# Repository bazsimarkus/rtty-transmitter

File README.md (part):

# rtty-transmitter

An ATmega328P-based AM/RTTY transmitter card with USB serial control, Direct Digital Synthesis audio generation, PCM audio playback from SPI EEPROM, and a Wien bridge oscillator RF stage. The board is controlled entirely through an AT command interface over a virtual COM port, and includes a companion Python control center application for Windows, Linux, and macOS.

---

## Table of Contents

- [Overview](#overview)
- [Features](#features)
- [Hardware Description](#hardware-description)
  - [USB Interface and Power Supply](#usb-interface-and-power-supply)
  - [Microcontroller](#microcontroller)
  - [DAC and DDS Engine](#dac-and-dds-engine)
  - [EEPROM for PCM Audio Storage](#eeprom-for-pcm-audio-storage)
  - [Virtual Ground](#virtual-ground)
  - [Wien Bridge Oscillator and Carrier Wave](#wien-bridge-oscillator-and-carrier-wave)
  - [Audio Buffer](#audio-buffer)
  - [RF Output Stage](#rf-output-stage)
  - [Tank Circuit and Antenna Output](#tank-circuit-and-antenna-output)
  - [Signal Chain Summary](#signal-chain-summary)
  - [GPIO Expansion and Status LED](#gpio-expansion-and-status-led)
  - [Bill of Materials](#bill-of-materials)
  - [PCB](#pcb)
- [Firmware](#firmware)
  - [AT Command Interface](#at-command-interface)
  - [RTTY Encoding](#rtty-encoding)
  - [PCM Audio Playback](#pcm-audio-playback)
  - [EEPROM Upload Protocol](#eeprom-upload-protocol)
- [Getting Started](#getting-started)
  - [Requirements](#requirements)
  - [Drivers](#drivers)
  - [Connecting the Board](#connecting-the-board)
- [Building and Flashing the Firmware](#building-and-flashing-the-firmware)
  - [Command-Line Build with avr-gcc and avrdude](#command-line-build-with-avr-gcc-and-avrdude)
  - [Building with MPLAB X IDE](#building-with-mplab-x-ide)
- [Control Center Application](#control-center-application)
  - [Installation](#installation)
  - [Usage](#usage)
- [Antenna Selection and Range](#antenna-selection-and-range)
- [Testing and Reception](#testing-and-reception)
- [Comparison with Official RTTY](#comparison-with-official-rtty)
- [Regulatory Notice](#regulatory-notice)
- [Personal Note](#personal-note)

---

## Overview

This project is a self-contained AM/RTTY transmitter card designed and built around the ATmega328P microcontroller. The board generates FSK (Frequency Shift Keying) audio tones using a software Direct Digital Synthesis engine, feeds those tones through an 8-bit SPI DAC, buffers and amplifies them through a dual op-amp stage, and then modulates them onto a carrier wave produced by a Wien bridge oscillator running at approximately 802 kHz. The resulting AM signal is delivered to an SMA connector for antenna connection.

The board is powered and controlled through a single USB Type B cable. An MCP2221A USB-to-UART bridge makes the board appear as a standard COM port on the host computer, requiring no custom drivers beyond the standard MCP2221 package. All board functions are controlled through a straightforward AT command interface at 9600 baud. A Python-based control center application is included in the tools folder to provide a graphical interface for all features, including RTTY message transmission, text file transmission, PCM audio upload and playback, and GPIO control.

The board can also function as an audio transmitter: an 8-bit, 8 kHz PCM audio file can be uploaded to the onboard 25LC1024 SPI EEPROM (128 KB) and played back over the air using the AT+play command, AM-modulating the 802 kHz carrier with audio content.

---

## Features

- RTTY transmission using ITA-2 Baudot encoding over AM
- Configurable mark/space frequencies and baud rate via AT commands (defaults: MARK 2125 Hz, SPACE 2295 Hz, 45.45 baud)
- Direct Digital Synthesis sine wave generation at 80 kHz sample rate via Timer1 interrupt
- MCP4901 8-bit SPI DAC output
- 25LC1024 SPI EEPROM (128 KB) for PCM audio sample storage
- 8 kHz PCM audio playback from EEPROM via Timer2 interrupt, AM-modulating the carrier
- Wien bridge oscillator carrier wave at approximately 802 kHz
- Current-modulated cascode RF output stage (PN2222A BJTs)
- Tank circuit output filter with loading coil and SMA antenna connector
- MCP2221A USB-to-UART bridge, appearing as a standard COM port at 9600 8N1
- Powered entirely from USB (5V, USB Type B connector)
- Five user-accessible GPIO pins on a 2x5 pin header (J3), including onboard status LED control
- AVR ISP 10-pin shrouded box header for firmware flashing with USBasp or compatible programmer
- 120 x 60 mm, two-layer FR-4 PCB, designed in KiCad 7 and finalized in KiCad 9
- Companion Python control center application for Windows, Linux, and macOS

---

## Hardware Description

### USB Interface and Power Supply

The board is connected to a host PC through a USB Type B connector (J1). Power is drawn from the USB 5V rail and distributed across the board through decoupling capacitors at each IC supply pin.

The USB-to-UART bridge is the MCP2221A (U1), a 14-pin DIP chip from Microchip. When connected, it presents itself to the operating system as a virtual COM port, allowing any standard serial terminal or the included control center application to communicate with the ATmega328P at 9600 8N1. No special kernel modules are required on most systems, though the MCP2221 driver package from Microchip's website may need to be installed on Windows for the COM port to appear. The driver can be downloaded from Microchip's product page for the MCP2221A.

### Microcontroller

The central processing element is the ATmega328P (U2), a 28-pin DIP AVR microcontroller running from a 16 MHz crystal (Y1) with no clock prescaler. It handles all firmware tasks: UART communication with the host through the MCP2221A, hardware SPI to the MCP4901 DAC, bit-bang SPI to the 25LC1024 EEPROM, GPIO control, and the two timer-driven interrupt service routines that form the core of the signal generation pipeline.

The reset line is connected through a capacitor to the DTR signal of the MCP2221A, allowing the control center application to reset the board on connect. A 10-pin shrouded box header (J2) exposes the AVR ISP signals (RESET, SCK, MISO, MOSI) for firmware flashing with a USBasp or compatible programmer.

### DAC and DDS Engine

The MCP4901 (U3) is an 8-bit, single-channel SPI DAC in an 8-pin DIP package. It receives samples from the ATmega328P over hardware SPI running at 8 MHz (F_CPU/2 with SPI2X). Timer1 is configured in CTC mode with OCR1A = 199 and no prescaler, producing an interrupt rate of exactly 80 kHz (16 MHz / 200). Each interrupt advances a 32-bit DDS phase accumulator by a pre-computed increment that determines the output frequency:

```
phase_increment = frequency x 2^32 / 80000
```

The upper 8 bits of the phase accumulator index into a 256-entry sine table stored in SRAM, and the resulting sample is written to the DAC in the same ISR. This produces a clean, digitally synthesized sine wave at the desired audio frequency with a sample rate of 80 kHz, giving well over 40 kHz of usable bandwidth and negligible harmonic content in the RTTY audio band. Setting the phase increment to zero mutes the carrier between transmissions.

For RTTY, the firmware uses two phase increments corresponding to the mark and space frequencies. Bit timing is achieved by loading a tick counter in the same ISR: for 45.45 baud, each bit lasts 80000 / 45.45 = 1760 Timer1 ticks, which equals exactly 22 ms.

### EEPROM for PCM Audio Storage

The 25LC1024 (U4) is a 1 Mbit (131072 byte) SPI EEPROM in an 8-pin DIP package. It is connected to the ATmega328P through a bit-bang SPI interface on PORTC (PC0 = /CS, PC3 = MOSI, PC4 = SCK, PC5 = MISO). A separate bit-bang interface is used for the EEPROM rather than the hardware SPI port so that the hardware SPI bus remains dedicated to the DAC and the time-critical 80 kHz Timer1 ISR is not disrupted by EEPROM accesses.

The EEPROM stores 8-bit unsigned PCM audio samples at 8 kHz. During playback, Timer1 is suspended and Timer2 takes over, configured in CTC mode to fire at exactly 8 kHz (OCR2A = 249, prescaler /8 on a 16 MHz clock). Each Timer2 ISR reads one byte from the EEPROM via bit-bang SPI and writes it directly to the DAC, producing an audio waveform that AM-modulates the carrier. End of audio is signaled by 250 consecutive 0xFF samples, which at 8 kHz corresponds to approximately 31 ms of silence, making it a reliable sentinel value.

### Virtual Ground

The MCP6022 op-amp and the rest of the analog circuit are powered from a single 5V USB supply, which means the supply voltage goes from 0V (GND) to 5V and nothing below. The problem is that a sine wave needs to swing both up and down around a center point. If the center point is 0V, the negative half of the wave would require a negative voltage, which we simply don't have.

The solution is to create a "virtual ground" at 2.5V, a stable mid-point that the op-amp can treat as its reference. The sine wave then swings from around 1.5V up to 3.5V, which looks like ±1V when measured relative to this 2.5V center. The next stage (the transistor base) receives the signal through a coupling capacitor, which strips away the 2.5V DC offset and leaves only the AC swing.

R15 (10k) and R16 (10k) form a simple voltage divider between the 5V supply and GND. Because both resistors are the same value, the midpoint sits at exactly 2.5V. C17 (10uF) is a bypass capacitor connected from this midpoint to GND. It acts like a reservoir that keeps the 2.5V stable and prevents it from wobbling when the op-amp draws current from it. Without this capacitor, the virtual ground voltage would fluctuate with the signal, causing distortion. The virtual ground node is labeled VIRTUAL GROUND in the schematic and is accessible at test point TP1 on the PCB.

### Wien Bridge Oscillator and Carrier Wave

The carrier wave is generated by the first op-amp inside the MCP6022 chip (U5A). It is wired as a Wien bridge oscillator, which is a circuit that produces a sine wave on its own with no input signal (it just runs continuously once power is applied).

The basic idea is that the op-amp has two feedback paths. The first path goes from the output back to the non-inverting input (the "+" pin) and is frequency-selective (it only passes signals at one specific frequency with the right timing to keep the oscillation going). The second path goes from the output back to the inverting input (the "−" pin) and sets the gain. If the gain is slightly above 1 at that specific frequency, the circuit amplifies its own tiny noise until it builds into a stable sine wave.

The frequency is set by R23 (1.5k) and R14 (1.5k) together with C18 (100pF) and C15 (100pF). These four components form the frequency-selective network on the non-inverting input. One resistor-capacitor pair (R14 and C15) connects from the non-inverting input to the virtual ground. The other pair (R23 and C18) connects from the non-inverting input back to the output. This arrangement only passes the right frequency and phase combination to keep the oscillator running. The resonant frequency works out to approximately 802 kHz, which sits in the AM medium-wave broadcast band, meaning any standard AM kitchen radio can receive the signal without special equipment.

```
f = 1 / (2 x pi x R x C)
  = 1 / (2 x pi x 1500 x 100e-12)
  = approximately 802 kHz
```

The gain is set by R22 (15k) and R19 (4.7k). R19 connects from the inverting input ("−" pin, pin 2) to the virtual ground, and R22 connects from the inverting input back to the output. The ratio of these two resistors sets the amplification to just above 3, which is the minimum needed to sustain oscillation in a Wien bridge.

The problem with setting the gain slightly above 3 is that without any correction, the wave would just keep growing until it hits the supply rails and becomes a clipped square wave rather than a clean sine. To prevent this, D5 and D6 (both 1N4148 signal diodes) are connected in anti-parallel (meaning one diode faces one direction and the other faces the opposite direction), together with R24 (10k) in series with them. This whole parallel block sits in parallel with R22. When the oscillation amplitude is small, the diodes don't conduct and R22 does the feedback job on its own. As the amplitude grows and the peaks get tall enough to forward-bias the diodes (around 0.6V), they start conducting and effectively lower the feedback resistance, which brings the gain back down and stops the wave from growing further. This keeps the output as a clean, stable sine wave at about 2V peak-to-peak.

The MCP6022 was chosen because it is a rail-to-rail op-amp, meaning its output can swing all the way to 0V and 5V, and it has enough speed (10 MHz gain-bandwidth product) to still have useful gain at 802 kHz.

The output of the oscillator comes out of pin 1 of U5 and is labeled CARRIER WAVE in the schematic. It is accessible at test point TP3 on the PCB. The frequency counter measurement below was taken directly at TP3 on the assembled board.

### Audio Buffer

The second op-amp inside the MCP6022 (U5B) takes the audio signal from the DAC and prepares it for the RF output stage.

The DAC output connects through R12 (1k) and C13 (10uF) to form a low-pass RC filter that smooths out the stepped output of the DAC, followed by AC coupling into the op-amp. R17 (2.2k) connects the non-inverting input (pin 5) to the virtual ground, which biases the input to the 2.5V midpoint so the op-amp is correctly centered. R20 (10k) and R21 (10k) set the gain: R21 connects from the inverting input (pin 6) to the virtual ground, and R20 connects from the inverting input back to the output (pin 7). With both resistors the same value, the gain works out to 2, which doubles the audio signal amplitude before it reaches the transistor stage. C16 (10uF) at the output AC-couples the buffered signal, stripping the 2.5V DC offset before the signal reaches the transistor base.

The buffered audio signal is accessible at test point TP4 on the PCB.

### RF Output Stage

This is where amplitude modulation actually happens. The carrier wave from the Wien bridge oscillator and the buffered audio signal from the op-amp come together in a two-transistor circuit built around Q1 and Q2 (both PN2222A NPN transistors).

Think of the circuit as a single pipe carrying current from the 5V supply down to GND. Q1 sits at the top of the pipe and Q2 sits at the bottom, stacked in series.

Q2 is the audio transistor. Its base receives the buffered audio signal through C7 (10uF), a coupling capacitor that passes AC audio while blocking DC. R9 (470R) connects the base to the 5V supply and R10 (220R) connects it to GND. These two resistors together form a bias voltage divider that holds the base at about 2V when no audio signal is present, keeping Q2 partially open at all times. This is important because if Q2 were completely off when the audio signal is at its lowest point, the output would cut out and you would hear distortion. The audio signal riding on top of this 2V bias makes Q2 open and close gradually, controlling how much current flows through the bottom of the pipe at audio frequencies. R11 (100R) is the emitter resistor, sitting between the emitter of Q2 and GND. Without it, a small rise in temperature would make Q2 conduct more, which heats it up further, which makes it conduct even more, a runaway loop that would destroy the transistor. R11 limits the maximum current and breaks that loop.

Q1 is the RF transistor. Its base receives the 802 kHz carrier sine wave from the oscillator through C6 (100pF), a coupling capacitor for the RF signal. R7 (22k) connects the base to the 5V supply and R8 (10k) connects it to GND, forming the bias voltage divider that keeps Q1 in the right operating region. The carrier drives Q1 to switch on and off 802,000 times per second, chopping the current in the pipe at the carrier frequency.

The result of stacking Q1 on top of Q2 is that Q1 chops the current into rapid RF pulses, but the size of those pulses is controlled by how open Q2 is, which follows the audio waveform. On an oscilloscope, the output at Q1's collector looks like a 802 kHz sine wave that grows and shrinks in amplitude following the audio signal. That is amplitude modulation.

L1 (1mH) is an RF choke, an inductor specifically used to block high-frequency signals from travelling somewhere they shouldn't. It connects between the 5V supply and Q1's collector. It has almost zero DC resistance, so it passes the full supply voltage to the transistors without dropping it. But at 802 kHz, a 1mH inductor has an impedance of roughly 5000 ohms, and it acts like a wall for RF. So the RF signal generated at Q1's collector cannot go back toward the power supply through L1. Instead it is forced to flow out through C10 (100nF) toward the antenna. As a side effect, L1 also lets Q1's collector voltage momentarily swing higher than 5V due to inductive kickback, which increases the available output swing.

Before building the circuit on PCB, the two-transistor cascode AM modulator was simulated in LTspice to verify that the topology produces a clean AM output. The simulation confirmed the expected behaviour: a carrier wave whose envelope is cleanly modulated by the audio signal, with no overmodulation or clipping. The LTspice project file is included in the ltspice folder of the repository.

### Tank Circuit and Antenna Output

After Q1's collector, the signal passes through a small matching network before reaching the antenna connector.

C10 (100nF) is a DC blocking capacitor, and its job is to pass AC signals while stopping DC from getting through. Q1's collector sits at roughly 5V DC because L1 feeds the supply voltage directly with no resistive drop. C10 blocks this DC so it never reaches the antenna connector, while passing the 802 kHz AC signal through easily (at 802 kHz a 100nF capacitor has only about 2 ohms of impedance, so it is essentially invisible to the signal).

After C10, the signal arrives at a node where C12 (1nF) connects to GND and L2 (330uH) continues in series toward the antenna. C12 and L2 together form a resonant tank circuit. At 802 kHz, L2 and C12 resonate, meaning they create a high-impedance "bandpass" effect at the carrier frequency that suppresses harmonics and other noise products from the transistor stage. This keeps the transmitted spectrum relatively clean.

L2 (330uH) also serves as a loading coil, sometimes called a base-loading inductor. The antennas this board is designed to use are very short (maybe 0.3 to 1 meter) compared to a proper quarter-wave antenna at 802 kHz, which would need to be about 93 meters long. A short antenna looks like a small capacitor to the circuit, with very high impedance, and most of the RF energy would just bounce back rather than radiate. L2 introduces an inductive reactance that partially cancels out this capacitive effect, making the short antenna behave more like a resistive load and allowing more of the power to actually be radiated.

The output of L2 connects to J7, a vertical SMA female connector on the edge of the board, where any standard SMA antenna can be attached.

### Signal Chain Summary

Now that all the individual blocks have been described, the complete signal path from firmware to antenna is:

```
DDS engine (Timer1 ISR, 80 kHz)
  --> MCP4901 DAC (hardware SPI, 8 MHz)
    --> R12 --> op-amp buffer (U5B)
      --> RF output stage (Q2 audio transistor / Q1 RF transistor cascode)
        --> C10 DC block (100 nF) --> L2 loading coil (330 uH) / C12 tank (1 nF)
          --> SMA antenna connector (J7)

Audio playback path (Timer2 ISR, 8 kHz):
  25LC1024 EEPROM --> bit-bang SPI read --> MCP4901 DAC --> same path as above

Carrier wave (continuous, hardware oscillator):
  Wien bridge oscillator (U5A, R15/R16/C6/C15) --> Q1 base via 1 nF capacitor
```

### GPIO Expansion and Status LED

Five GPIO pins (PD2 through PD6, mapped as AT command pins 0 through 4) are brought out to the 2x5 female pin socket header J3. These pins are configured as outputs and can be driven high or low through the AT+write command, making them available for user applications such as driving relays, LEDs, or interfacing with other hardware.

The onboard status LED (D4, white 5mm LED) is connected to PD7 through R6. It is mapped as GPIO pin 5 in the AT command interface and lights automatically during RTTY transmission, EEPROM upload, and audio playback. It can also be controlled directly with AT+write=5,1 and AT+write=5,0.

A tactile reset button (S1, 6x6mm) is connected to the ATmega328P reset line for manual resets without needing to disconnect USB.

### Bill of Materials

| Reference | Qty | Value / Part |
|---|---|---|
| U1 | 1 | MCP2221A-I/P (USB-UART bridge, DIP-14) |
| U2 | 1 | ATmega328P-P (MCU, DIP-28) |
| U3 | 1 | MCP4901 (8-bit SPI DAC, DIP-8) |
| U4 | 1 | 25LC1024 (1 Mbit SPI EEPROM, DIP-8) |
| U5 | 1 | MCP6022 (dual rail-to-rail op-amp, DIP-8) |
| Q1, Q2 | 2 | PN2222A (NPN BJT, TO-92) |
| Y1 | 1 | 16 MHz crystal (HC49-U) |
| L1 | 1 | 1 mH radial inductor |
| L2 | 1 | 330 uH radial inductor |
| D1 | 1 | LED 5mm Yellow |
| D2 | 1 | LED 5mm Green |
| D3 | 1 | LED 5mm Red |
| D4 | 1 | LED 5mm White |
| D5, D6 | 2 | 1N4148 signal diode |
| J1 | 1 | USB Type B connector |
| J2 | 1 | 2x5 shrouded box header (AVR ISP) |
| J3 | 1 | 2x5 female pin header (GPIO) |
| J7 | 1 | SMA vertical female connector |
| S1 | 1 | Tactile button 6x6mm |
| C1,C4,C8,C10,C14,C19 | 6 | 100nF |
| C2 | 1 | 470nF |
| C3,C7,C13,C16,C17 | 5 | 10uF electrolytic |
| C5, C9 | 2 | 22pF (crystal load) |
| C6,C15,C18 | 3 | 100pF |
| C11 | 1 | 10nF |
| C12 | 1 | 1nF |
| R1,R2,R8,R13,R15,R16,R18,R20,R21,R24 | 10 | 10k |
| R3,R4,R5,R9 | 4 | 470R |
| R6, R12 | 2 | 1k |
| R7 | 1 | 22k |
| R10 | 1 | 220R |
| R11 | 1 | 100R |
| R14, R23 | 2 | 1.5k |
| R17 | 1 | 2.2k |
| R19 | 1 | 4.7k |
| R22 | 1 | 15k |

### PCB

The PCB is a two-layer FR-4 board measuring 120 x 60 mm, 1.6 mm thick. It was designed in KiCad 7 and the project was finalized in KiCad 9. The board was manufactured by JLCPCB with green soldermask, white silkscreen, HASL (leaded) surface finish, and 1 oz outer copper weight. All components are through-hole for ease of hand assembly. Gerber files, drill files, and the complete KiCad project files are included in the schematic folder of this repository.

---

## Firmware

The firmware is a single C source file (rtty-transmitter/main.c), written for avr-gcc and targeting the ATmega328P at 16 MHz. It has no external library dependencies beyond the standard avr-libc. The current version is v1.0.0.

Once the board is connected and the MCP2221 driver is installed (see the Getting Started section), it appears as a standard COM port on the host computer. From that point, any serial terminal program can be used to communicate with it directly: PuTTY, Tera Term, the Arduino Serial Monitor, minicom on Linux, or the built-in terminal of any IDE. Set the port to 9600 baud, 8 data bits, no parity, 1 stop bit (9600 8N1). On connecting and pressing Enter, the firmware prints a startup banner listing all available commands and the current defaults. No special software is needed to use the board at a basic level.

### AT Command Interface

The firmware communicates at 9600 8N1. Commands are typed as plain text and terminated with a carriage return (Enter key in any terminal). All commands start with the letters AT, which stands for "attention" and is a convention inherited from classic modem command sets. The board echoes each character as you type it, so you can see what you are entering. It responds with OK on success or Error: ... on failure.

| Command | Description |
|---|---|
| AT | Echo test. Returns OK if the board is responsive. |
| AT+send="message" | Encode and transmit message as Baudot RTTY. Message is converted to upper case. Characters not representable in ITA-2 are silently skipped. |
| AT+set=param,value | Set a runtime parameter. Valid parameters: high (mark frequency in Hz), low (space frequency in Hz), baud (baud rate, e.g. 45.45). |
| AT+get=param | Query the current value of a parameter. Valid parameters: high, low, baud. |
| AT+write=pin,value | Set a GPIO pin. Pin 0-4 map to PD2-PD6 (header J3). Pin 5 controls the status LED on PD7. Value is 0 or 1. |
| AT+play | Play the 8-bit PCM audio stored in EEPROM. Suspends Timer1 and uses Timer2 at 8 kHz. Ends automatically when 250 consecutive 0xFF bytes are encountered. |
| AT+upload | Enter EEPROM upload mode. Accepts raw hex bytes (space or newline separated, e.g. A3 4F 00 ...) and writes them to the EEPROM starting at address 0. The session ends automatically after a configurable idle timeout with no incoming data. |
| AT+reset | Restore factory defaults: MARK = 2125 Hz, SPACE = 2295 Hz, BAUD = 45.45. |
| AT+help | Print a full command reference to the serial terminal. |

Default parameters on startup:

```
MARK  = 2125 Hz
SPACE = 2295 Hz
BAUD  = 45.45
```

These are the standard ITA-2 tones used in traditional 45.45 baud RTTY, chosen for maximum compatibility with RTTY decoders.

A few practical examples to get started quickly:

```
AT
```
Expected response: OK. Use this to confirm the board is alive and the COM port is working.

```
AT+send="HELLO WORLD"
```
Encodes and transmits the text as a Baudot RTTY burst. The status LED lights during transmission.

```
AT+set=baud,50
AT+set=high,2125
AT+set=low,2295
```
Changes the baud rate to 50 baud (another common RTTY speed) while keeping the standard tones.

```
AT+get=baud
```
Reads back the current baud rate. The board will respond with the numeric value followed by OK.

```
AT+write=5,1
AT+write=5,0
```
Turns the onboard status LED on, then off.

```
AT+play
```
Plays the audio sample stored in EEPROM over the AM carrier. Make sure an audio file has been uploaded first with AT+upload or the control center application.

### RTTY Encoding

RTTY (Radio Teletype) is a digital text transmission mode where each character is encoded as a series of tones. This board uses the ITA-2 standard, also called Baudot, which dates back to early telegraph and teletype machines. Understanding how Baudot works helps in understanding what the firmware is actually doing when you call AT+send.

Baudot is a five-bit code. Five bits can represent 32 different combinations (2 to the power of 5). That is not enough for the full alphabet plus digits plus punctuation. The solution is to have two separate tables of 32 characters each: the Letters table (LTRS) and the Figures table (FIGS). A special shift code switches the decoder between the two tables, much like holding Shift on a keyboard. The transmitter sends a LTRS code before a run of letters, and a FIGS code before a run of numbers or punctuation.

Here are the two tables as implemented in the firmware:

Letters table (LTRS shift active):

| Code  | Char | Code  | Char | Code  | Char | Code  | Char |
|-------|------|-------|------|-------|------|-------|------|
| 11000 | A    | 10011 | B    | 01110 | C    | 10010 | D    |
| 10000 | E    | 10110 | F    | 01011 | G    | 00101 | H    |
| 01100 | I    | 11010 | J    | 11110 | K    | 01001 | L    |
| 00111 | M    | 00110 | N    | 00011 | O    | 01101 | P    |
| 11101 | Q    | 01010 | R    | 10100 | S    | 00001 | T    |
| 11100 | U    | 01111 | V    | 11001 | W    | 10111 | X    |
| 10101 | Y    | 10001 | Z    | 00100 | SP   | 01000 | LF   |

Figures table (FIGS shift active):

| Code  | Char | Code  | Char | Code  | Char | Code  | Char |
|-------|------|-------|------|-------|------|-------|------|
| 11000 | -    | 10011 | ?    | 01110 | :    | 10010 | $    |
| 10000 | 3    | 10110 | !    | 01011 | &    | 00101 | #    |
| 01100 | 8    | 11010 | (    | 11110 | )    | 01001 | .    |
| 00111 | ,    | 00110 | 9    | 00011 | 0    | 01101 | 1    |
| 11101 | 1    | 01010 | '    | 10100 | 5    | 00001 | 7    |
| 11100 | 7    | 01111 | ;    | 11001 | 2    | 10111 | /    |
| 10101 | 6    | 10001 | "    | 00100 | SP   | 01000 | LF   |

As an example, to send the letter H, the firmware looks up 00101 in the LTRS table and transmits those five bits. To then send the digit 3, it first sends the FIGS shift code 11011, then transmits 10000 (which means 3 in the FIGS table).

Each five-bit character code is framed with a start bit and stop bits in the same way a UART serial protocol works: one start bit (mark tone, logical 0), the five data bits, and two stop bits (space tone, logical 1). On the receiving end, a RTTY decoder listens for the start bit transition to synchronize, then samples the five data bits, then waits for the stop bits before looking for the next start bit. The firmware also sends a carriage return and a line feed as a preamble before each message so the receiving decoder has time to lock on.

Bit timing is derived directly from the 80 kHz Timer1 tick rate. For 45.45 baud, each bit period is 1760 Timer1 ticks (80000 / 45.45 = 1760), which corresponds exactly to 22 ms per bit. The firmware spins on the tick countdown in the ISR, so bit timing is cycle-accurate regardless of main-loop activity. The baud rate can be changed with AT+set=baud,value to any value the DDS can produce at that tick resolution.

### PCM Audio Playback

The board can transmit audio over the AM carrier, not just RTTY tones. The audio is stored in the onboard EEPROM as raw PCM samples and played back by the AT+play command.

PCM (Pulse Code Modulation) is the simplest digital audio format: every sample is a number representing the amplitude of the sound at that instant in time. The firmware uses 8-bit unsigned PCM at 8 kHz, which means each sample is a single byte (0-255, where 128 represents silence/midpoint), and 8000 samples are played per second. This is the same format as old telephone audio and is perfectly adequate for speech and simple sounds. The maximum recording length is 131072 bytes divided by 8000 samples per second, which gives approximately 16.4 seconds of audio.

Four ready-to-use sample files are included in the `assets/pcm-samples` directory and can be uploaded directly through the control center without any conversion. Three are music clips (`dance-electronic.raw`, `energetic-rock.raw`, `pop-upbeat.raw`), and one is a 1 kHz sine wave (`sine-1khz.raw`) useful for testing and verifying the audio chain. Of course, any audio can also be converted from any source using Audacity as described in the following section.

To prepare an audio file for upload, use Audacity (free, available at https://www.audacityteam.org):

1. Open your audio file in Audacity, or record directly.
2. If the audio is stereo, go to Tracks > Mix > Mix Stereo Down to Mono.
3. In the bottom-left of the track, set the sample rate to 8000 Hz.
4. Go to File > Export Audio.
5. In the export dialog, select "Other uncompressed files" as the format.
6. Click Options and set Header to "RAW (header-less)" and Encoding to "Unsigned 8-bit PCM."
7. Save the file with any name (for example, audio.raw).

The resulting .raw file is the exact binary data that needs to be uploaded to the EEPROM.

During AT+play, the firmware suspends Timer1 (which drives the DDS engine and any in-progress RTTY transmission), starts Timer2 in CTC mode at exactly 8 kHz, and begins reading samples from the EEPROM one byte at a time via bit-bang SPI. Each sample is written directly to the MCP4901 DAC, which produces the audio waveform. This waveform feeds through the op-amp buffer and into the RF output stage, where it AM-modulates the 802 kHz carrier from the Wien bridge oscillator exactly as the DDS-generated RTTY tones do. The status LED lights for the entire duration of playback. After playback ends (detected by 250 consecutive 0xFF bytes, which serve as an end-of-audio marker), Timer2 is stopped, Timer1 is restarted, and the firmware returns to the AT command loop ready for the next command.

### EEPROM Upload Protocol

The AT+upload command puts the firmware into upload mode. The protocol is acknowledgement-driven: the host sends one 32-byte chunk at a time and waits for the board to respond before sending the next one. This guarantees reliable delivery regardless of how fast the host sends data.

The exact sequence is:

1. The host sends `AT+upload\r`.
2. The board responds with `READY\r\n` when it is ready to receive data.
3. The host sends raw data as exactly 64 ASCII hex characters (32 bytes encoded as hex pairs, no spaces or separators between characters in a chunk), for example `A34F00...`.
4. After processing each 32-byte chunk and writing it to the EEPROM page, the board responds with `>` to request the next chunk.
5. The host repeats steps 3-4 for each chunk.
6. After all chunks are sent, the host stops sending. The board's internal idle timeout (approximately 1.5 seconds) fires, it finalizes any remaining buffered page writes, and responds with `OK\r\n`.

The data is padded to a 32-byte boundary with 0xFF bytes before transmission. 0xFF is the erased state of EEPROM memory and also serves as the end-of-audio sentinel during playback (250 consecutive 0xFF bytes signal end of audio to the firmware).

The control center application handles all of this automatically. For users who want to write their own upload script, here is a minimal Python example that matches this exact protocol:

```python
import serial
import time

CHUNK_SIZE = 32   # 32 bytes per chunk = 64 hex characters sent per chunk

def upload_audio(port, raw_bytes):
    # Pad to a 32-byte boundary with 0xFF fill
    pad = CHUNK_SIZE - (len(raw_bytes) % CHUNK_SIZE)
    if pad != CHUNK_SIZE:
        raw_bytes += b'\xFF' * pad

    ser = serial.Serial(port, 9600, timeout=5)
    time.sleep(0.5)                          # Wait for board to reset on connect
    ser.reset_input_buffer()

    # Step 1: Send upload command and wait for READY
    ser.write(b"AT+upload\r")
    response = ""
    deadline = time.time() + 4.0
    while "READY" not in response and time.time() < deadline:
        response += ser.read(ser.in_waiting or 1).decode(errors="replace")
    if "READY" not in response:
        raise Exception("Board did not respond with READY")

    time.sleep(0.2)
    print("Board ready. Sending chunks...")

    # Step 2: Send data in 32-byte chunks, wait for '>' ack after each
    hex_data = raw_bytes.hex().upper()
    total_chunks = len(hex_data) // (CHUNK_SIZE * 2)

    for i, offset in enumerate(range(0, len(hex_data), CHUNK_SIZE * 2)):
        chunk_hex = hex_data[offset : offset + CHUNK_SIZE * 2]
        ser.write(chunk_hex.encode('ascii'))
        ser.flush()

        # Wait for the '>' acknowledgement from the board
        ack = ""
        deadline = time.time() + 5.0
        while '>' not in ack and time.time() < deadline:
            ack += ser.read(ser.in_waiting or 1).decode(errors="replace")
        if '>' not in ack:
            raise Exception(f"Timeout waiting for '>' at chunk {i}")

        print(f"  Chunk {i+1}/{total_chunks} OK")

    # Step 3: Wait for the board's idle timeout to fire and send final OK
    final = ""
    deadline = time.time() + 30.0
    while "OK" not in final and time.time() < deadline:
        final += ser.read(ser.in_waiting or 1).decode(errors="replace")

    print("Upload complete.")
    ser.close()

# Example usage:
with open("audio.raw", "rb") as f:
    data = f.read()

upload_audio("COM3", data)   # Replace COM3 with your port, e.g. /dev/ttyUSB0
```

The key point is that there is no fixed delay between chunks. The timing is entirely controlled by the board's `>` acknowledgement. The host only sends the next chunk after receiving `>`, which means the EEPROM page write cycle has already completed on the board side before the next chunk arrives.

---

## Getting Started

### Requirements

- ATmega328P-based board (this project)
- USB Type B cable
- A PC running Windows, Linux, or macOS
- Python 3.7 or later with the pyserial package (for the control center)
- avr-gcc and avrdude (for building and flashing firmware from the command line)
- A USBasp or compatible AVR ISP programmer (for firmware flashing)

### Drivers

On most Linux distributions no additional drivers are needed. On Windows, if the board does not appear as a COM port after connecting, install the MCP2221 driver from Microchip's website:

https://www.microchip.com/en-us/product/mcp2221a

### Connecting the Board

1. Connect the board to the PC with a USB Type B cable.
2. The power LED should illuminate.
3. On Windows, open Device Manager and confirm a new COM port has appeared under Ports (COM and LPT). On Linux the device will appear as /dev/ttyUSB0 or similar.
4. Open a serial terminal at 9600 8N1 (or launch the control center application) and press Enter. The firmware startup banner should appear, listing the available commands.

---

## Building and Flashing the Firmware

The firmware consists of a single source file: rtty-transmitter/main.c. No special IDE is required.

### Command-Line Build with avr-gcc and avrdude

Install avr-gcc and avrdude for your platform (on Debian/Ubuntu: `sudo apt install gcc-avr binutils-avr avrdude`; on Windows, install WinAVR or the Atmel toolchain).

Navigate to the rtty-transmitter directory and run:

```sh
avr-gcc -mmcu=atmega328p -DF_CPU=16000000UL -O1 \
    -funsigned-char -funsigned-bitfields \
    -ffunction-sections -fdata-sections \
    -fpack-struct -fshort-enums \
    -Wall -o main.elf main.c

avr-objcopy -O ihex main.elf main.hex
```

Then flash with your USBasp programmer:

```sh
avrdude -c usbasp -p m328p -U flash:w:main.hex
```

If avrdude reports a signature mismatch or permission error on Linux, ensure you are in the dialout group or run with sudo.

The final firmware image is approximately 10.4 KB, well within the ATmega328P's 32 KB Flash limit.

### Building with MPLAB X IDE

The repository includes an MPLAB X IDE project in the rtty-transmitter/nbproject directory. The project has two build configurations:

- default: Compiles only, produces the hex file.
- flash: Identical to default, but runs avrdude automatically after a successful build to flash the connected board via USBasp. The post-build step is:

```
avrdude -c usbasp -p m328p -U flash:w:${ImagePath}
```

where ImagePath is the MPLAB X macro pointing to the final production hex. With the flash configuration selected, clicking Build Main Project compiles the firmware and programs the board in a single step.

The project was developed with MPLAB X IDE v6.25 and the Microchip ATmega_DFP 3.3.279 device pack. The compiler used is avr-gcc from the Atmel Studio 7 toolchain.

A typical successful build and flash output looks like this:

```
avrdude: device signature = 0x1e950f (probably m328p)
avrdude: erasing chip
avrdude: writing 10444 bytes flash ...
Writing | ################################################## | 100% 4.62s
avrdude: 10444 bytes of flash verified
avrdude done.  Thank you.
BUILD SUCCESSFUL (total time: 10s)
```

---

## Control Center Application

The tools/rtty-transmitter-control-center.py Python script provides a graphical user interface for all board functions. It is built with Tkinter and requires no installation beyond Python 3 and the pyserial package.

### Installation

```sh
pip install pyserial
python tools/rtty-transmitter-control-center.py
```
### Usage

The window is split into two columns. The right column contains the command log and a Manual CMD entry field, both always visible. Outgoing commands appear in blue, board responses in green, system messages in grey, warnings in orange, and errors in red. The log can be cleared or saved with the buttons above it. Any AT command can be typed into the Manual CMD field and sent with Enter.
The left column has a connection bar at the top and four tabs below it. Select the COM port, click Refresh if needed, then click Connect. On a successful connection the status label turns green, the application sends an AT echo test, and reads back the current RTTY parameters automatically.

The RTTY Transmission tab covers sending messages and files. The text area at the top is pre-filled with a test pangram; edit it and click TRANSMIT MESSAGE to send. A Repetitions spinbox (1 to 1000) repeats the same message back to back, and Stop Transmission aborts an in-progress multi-repetition send. Below that, the Send Text File section lets you browse for a plain text file; once selected the application shows how many chunks it will be split into and the SEND FILE button becomes active. Files are filtered to the ITA-2 character set, newlines replaced with spaces, and split into 116-character chunks, each sent as a separate AT+send with acknowledgement before the next. At the bottom of the tab, the Current Parameters section shows the Mark, Space, and Baud values read from the board. Edit any field and click Apply to Board to update them, or Read from Board to refresh.

The Audio / EEPROM tab has a PLAY AUDIO button at the top that sends AT+play immediately. Below it, the Upload New Audio section lets you browse for an audio file. The application auto-detects raw binary (8-bit unsigned PCM at 8 kHz), a hex-dump text file, or a WAV file (WAV files trigger a warning since the header bytes will be included). After selecting a valid file within the 128 KB EEPROM limit, the file name, size, and estimated upload time are shown, and the Upload to EEPROM button becomes active. A progress bar and percentage label track the upload chunk by chunk.

The GPIO Control tab shows six panels in a 2x3 grid for GPIO 0 through GPIO 5 (PD2 through PD7). Each panel has a HIGH and a LOW button that sends the corresponding AT+write command immediately. GPIO 5 on PD7 is the onboard yellow status LED.

The System tab has three buttons: Check Connection (sends AT), Factory Reset (sends AT+reset), and Help (sends AT+help, printing the full command reference to the log).

---

## Antenna Selection and Range

The SMA connector (J7) accepts any standard SMA antenna. The board was tested with two antennas:

1. A generic ISM-band whip antenna primarily designed for 433/868/915 MHz use. While functional as a receive and general-purpose antenna, its electrical length is far shorter than the quarter-wave length at 802 kHz (approximately 93 meters), so it is not well matched to the transmit frequency and delivers limited range.

2. A telescopic SRH-789 multiband antenna, which can be extended to approximately 1 meter. This antenna performs noticeably better at 802 kHz, and with it a range of a few meters was achieved in testing. In one additional test, a length of SMA extension cable (approximately 1 meter) was inserted between the board's SMA connector and the SRH-789, effectively increasing the total radiating length. This further improved the range, demonstrating that even a simple increase in antenna conductor length has a measurable effect at medium-wave frequencies.

In both cases, a properly resonant loading coil or a ground-plane matched to the medium-wave band would significantly improve performance. With the default low-power output stage and a short antenna, the practical range of this board is limited to a few meters, which is entirely by design and appropriate for a bench demonstration or close-range testing setup.

Note that transmission in the AM medium-wave band is regulated in most countries. Always verify your local regulations before transmitting. See the Regulatory Notice section below.

---

## Testing and Reception

The board was tested using a standard portable AM/FM kitchen radio tuned to 802 kHz. With the radio placed within range, the RTTY tone bursts are clearly audible as alternating beeps corresponding to the mark and space tones.

For decoding, GRITTY 1.3 by Afreet Software was used. GRITTY is a free RTTY decoding program that processes the audio received by a soundcard and decodes the bit stream in real time. In the test setup, the radio received the AM signal and played back the audio tones, which were picked up by the laptop's built-in microphone and fed into GRITTY, which successfully decoded the transmitted text.

The AT+play audio playback function was also tested. A short 8-bit, 8 kHz PCM audio sample was uploaded to the EEPROM using the control center application and played back with AT+play. The audio was clearly audible through the kitchen radio receiver, with good intelligibility and no significant distortion. The 8 kHz sample rate is sufficient for voice and simple audio content, and the AM carrier does a faithful job of conveying the waveform at close range.

One observation during testing: the SPI interface between the ATmega328P and the EEPROM can produce noise that couples into the RF output, sometimes audible as a faint background interference. Standard bypass capacitors are placed at the relevant supply pins, but as with any RF design, further layout optimization and shielding can always improve results.

---

## Comparison with Official RTTY

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
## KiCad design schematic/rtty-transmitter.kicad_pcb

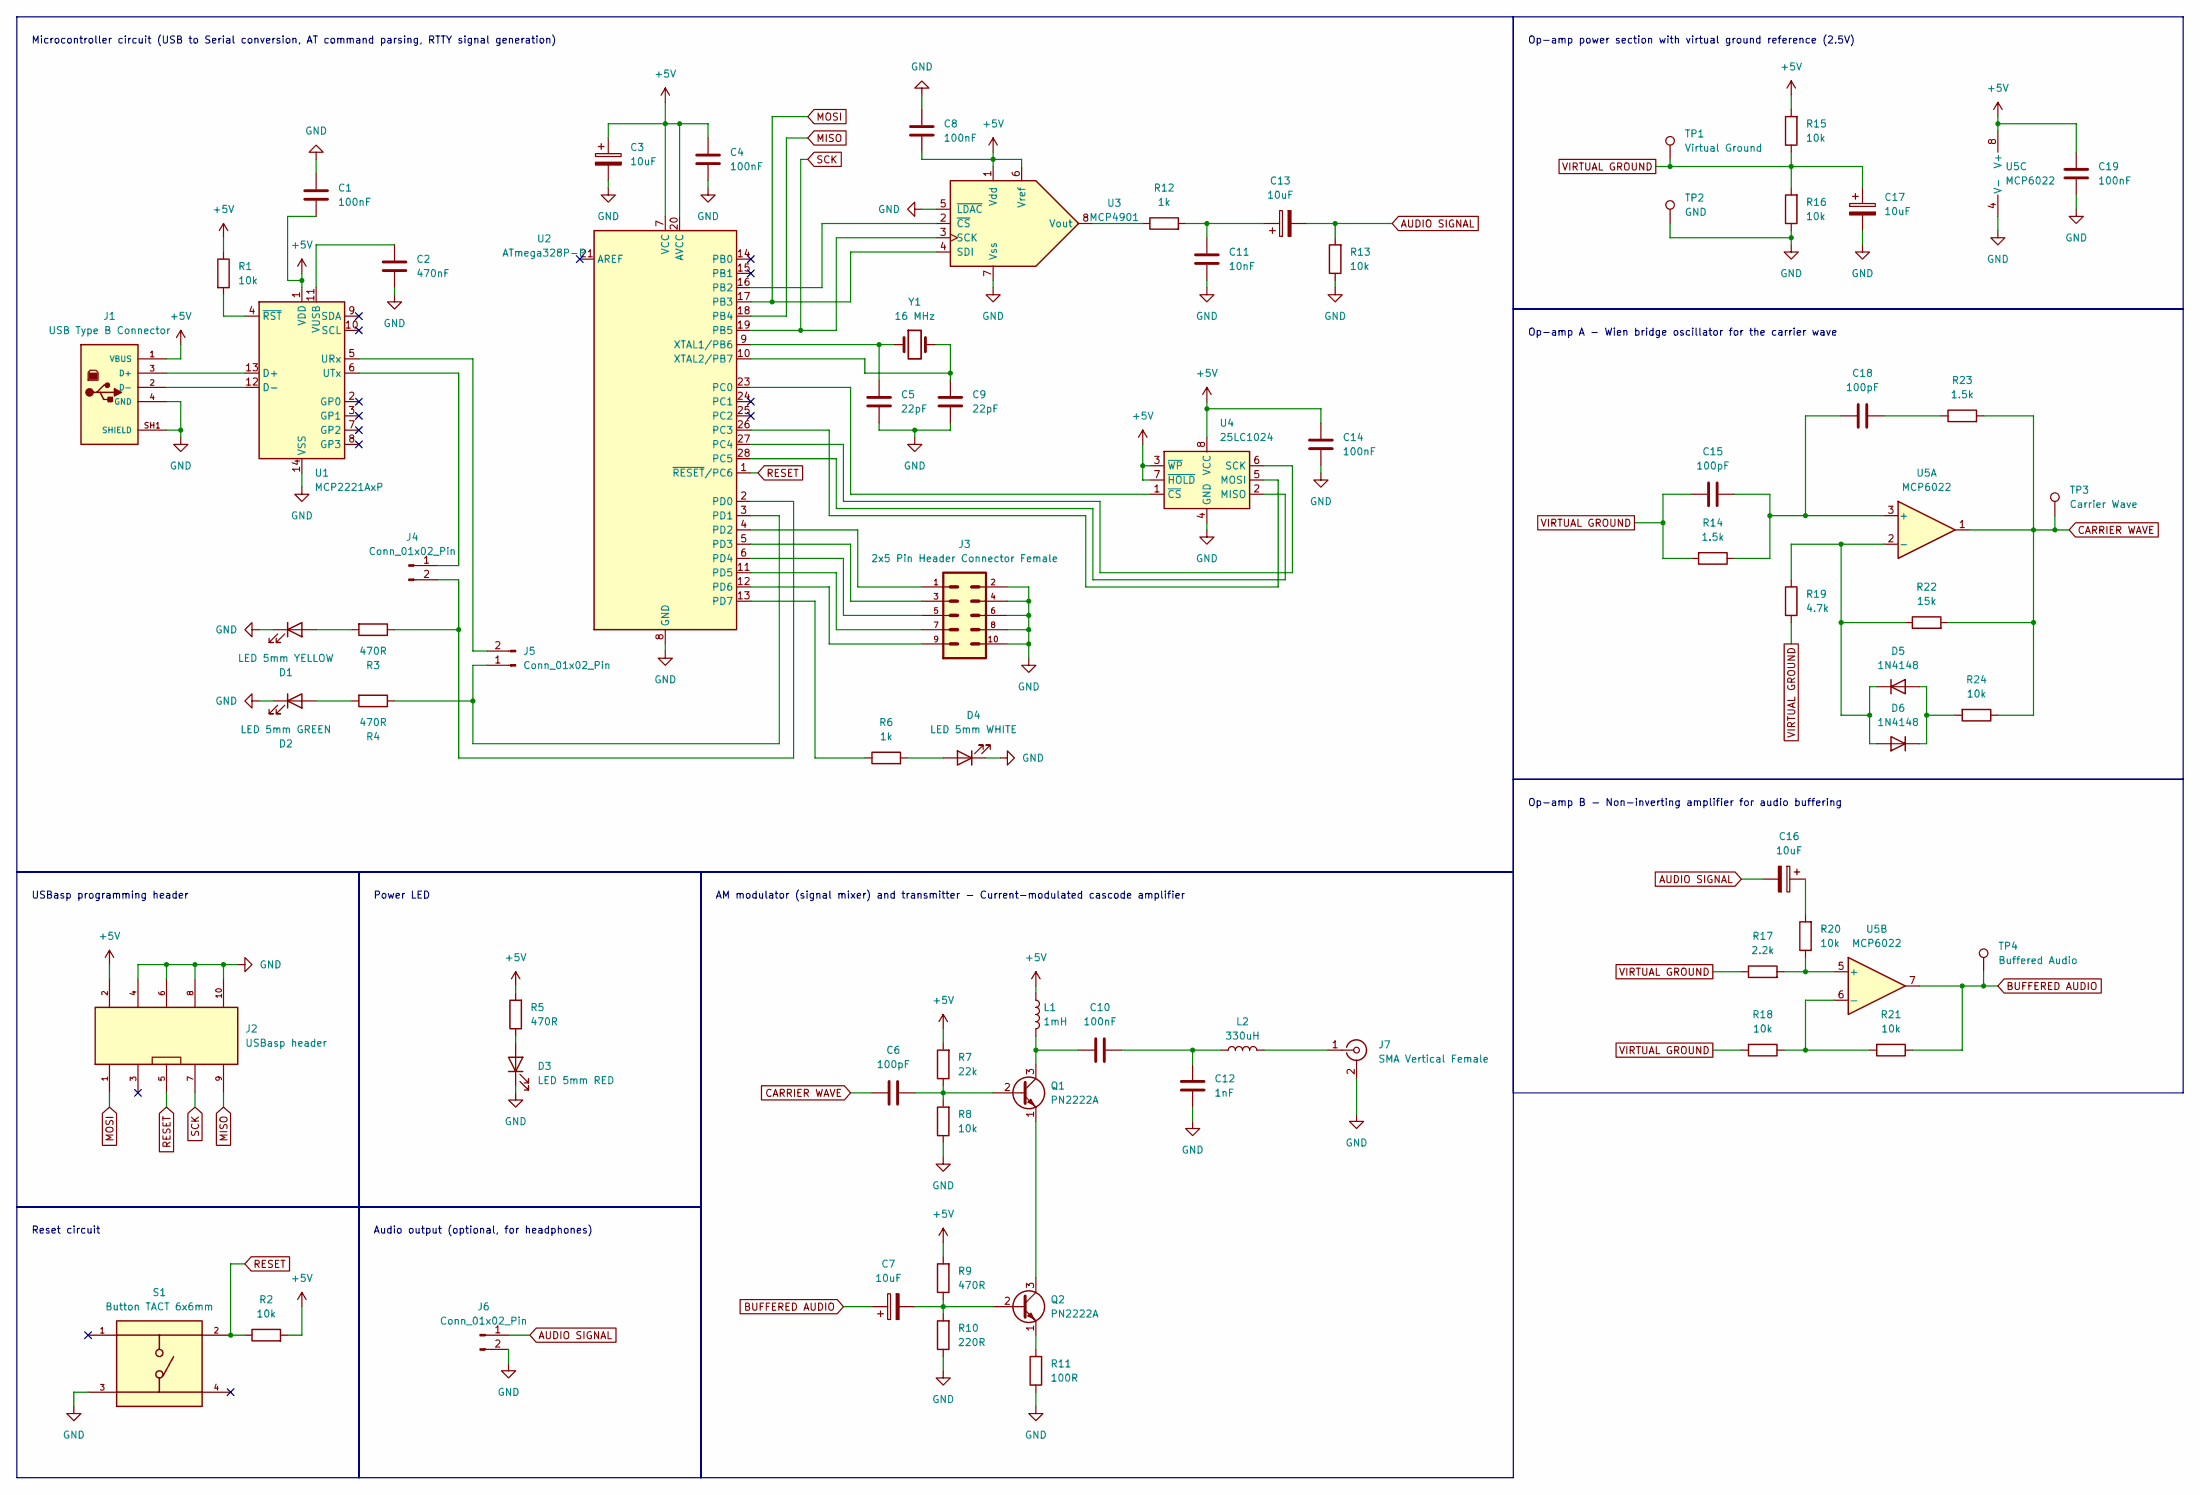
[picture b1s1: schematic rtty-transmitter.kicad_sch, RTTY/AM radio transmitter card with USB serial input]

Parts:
C1, C4, C8, C10, C14, C19: 100nF; C_100nF_L7.0mm_W2.5mm_P5.00mm
C2: 470nF; C_100nF_L7.0mm_W2.5mm_P5.00mm
C3, C7, C13, C16, C17: 10uF; CP_Radial_D5.0mm_P2.00mm
C5, C9: 22pF; C_Rect_L4.6mm_W2.0mm_P2.50mm_MKS02_FKP02
C6, C15, C18: 100pF; C_Disc_D3.0mm_W1.6mm_P2.50mm
C11: 10nF; C_Disc_D3.0mm_W1.6mm_P2.50mm
C12: 1nF; C_Disc_D3.0mm_W1.6mm_P2.50mm
D1: LED 5mm YELLOW; LED_D5.0mm_YELLOW
D2: LED 5mm GREEN; LED_D5.0mm_GREEN
D3: LED 5mm RED; LED_D5.0mm_RED
D4: LED 5mm WHITE; LED_D5.0mm_WHITE
D5, D6: 1N4148; D_DO-35_SOD27_P7.62mm_Horizontal
J1: USB Type B Connector; PART_REV 1.0
J2: USBasp header; 2x5 Shrouded Box Header
J3: 2x5 Pin Header Connector Female
J4, J5: Conn_01x02_Pin; PinHeader_1x02_P2.54mm_Vertical
J6: Conn_01x02_Pin; PinSocket_1x02_P2.54mm_Vertical
J7: SMA Vertical Female
L1: 1mH; L_Radial_D8.7mm_P5.00mm_Fastron_07HCP
L2: 330uH; L_Radial_D8.7mm_P5.00mm_Fastron_07HCP
Q1, Q2: PN2222A; TO-92_Inline
R1, R2, R8, R13, R15, R16, R18, R20, R21, R24: 10k; R_10k_Axial_DIN0207
R3, R4, R5, R9: 470R; R_470_Axial_DIN0207
R6, R12: 1k; R_1k_Axial_DIN0207
R7: 22k; R_10k_Axial_DIN0207
R10: 220R; R_10k_Axial_DIN0207
R11: 100R; R_10k_Axial_DIN0207
R14, R23: 1.5k; R_10k_Axial_DIN0207
R17: 2.2k; R_10k_Axial_DIN0207
R19: 4.7k; R_10k_Axial_DIN0207
R22: 15k; R_10k_Axial_DIN0207
S1: Button TACT 6x6mm; PARTREV 1.0
TP1: Virtual Ground; TestPoint_THTPad_D1.0mm_Drill0.5mm
TP2: GND; TestPoint_THTPad_D1.0mm_Drill0.5mm
TP3: Carrier Wave; TestPoint_THTPad_D1.0mm_Drill0.5mm
TP4: Buffered Audio; TestPoint_THTPad_D1.0mm_Drill0.5mm
U1: MCP2221AxP; DIP-14_W7.62mm
U2: ATmega328P-P; DIP-28_W7.62mm
U3: MCP4901; DIP-8_W7.62mm
U4: 25LC1024; DIP-8_W7.62mm
U5: MCP6022; DIP-8_W7.62mm
Y1: 16 MHz; Crystal_HC49-U_Vertical

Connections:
+5V: C1.2, C3.1, C4.1, C8.2, C14.1, C19.1, J1.1 (VBUS), J2.2, L1.1, R1.1, R2.2, R5.2, R7.2, R9.2, R15.2, U1.1 (VDD), U2.7 (VCC), U2.20 (AVCC), U3.1 (Vdd), U3.6 (Vref), U4.3 (~WP), U4.7 (~HOLD), U4.8 (VCC), U5.8 (V+)
AUDIO SIGNAL: C13.2, C16.2, J6.1, R13.2
BUFFERED AUDIO: C7.1, R21.1, TP4.1, U5.7
CARRIER WAVE: C6.2, R22.2, R23.2, R24.1, TP3.1, U5.1
GND: C1.1, C2.2, C3.2, C4.2, C5.2, C8.1, C9.2, C11.1, C12.2, C14.2, C17.2, C19.2, D1.1 (K), D2.1 (K), D3.1 (K), D4.1 (K), J1.4 (GND), J1.SH1 (SHIELD), J2.4, J2.6, J2.8, J2.10, J3.2, J3.4, J3.6, J3.8, J3.10, J6.2, J7.2 (Ext), R8.1, R10.1, R11.1, R13.1, R16.1, S1.3, TP2.1, U1.14 (VSS), U2.8 (GND), U2.22 (GND), U3.5 (~LDAC), U3.7 (Vss), U4.4 (GND), U5.4 (V-)
MISO: J2.9, U2.18 (PB4)
MOSI: J2.1, U2.17 (PB3), U3.4 (SDI)
unnamed: C10.2, C12.1, L2.1
unnamed: C11.2, C13.1, R12.2
unnamed: C16.1, R20.2
unnamed: C18.1, R23.1
unnamed: D1.2 (A), R3.2
unnamed: D2.2 (A), R4.2
unnamed: D3.2 (A), R5.1
unnamed: D4.2 (A), R6.2
unnamed: D5.2 (A), D6.1 (K), R24.2
unnamed: D5.1 (K), D6.2 (A), R19.1, R22.1, U5.2 (-)
unnamed: J1.3 (D+), U1.13 (D+)
unnamed: J1.2 (D-), U1.12 (D-)
unnamed: J4.1, U1.6 (UTx)
unnamed: J4.2, R3.1, U2.2 (PD0)
unnamed: J5.1, R4.1, U2.3 (PD1)
unnamed: J5.2, U1.5 (URx)
unnamed: J7.1 (In), L2.2
unnamed: C6.1, Q1.2 (B), R7.1, R8.2
unnamed: C10.1, L1.2, Q1.3 (C)
unnamed: Q1.1 (E), Q2.3 (C)
unnamed: C7.2, Q2.2 (B), R9.1, R10.2
unnamed: Q2.1 (E), R11.2
unnamed: C2.1, U1.11 (VUSB)
unnamed: R1.2, U1.4 (~RST)
unnamed: U2.16 (PB2), U3.2 (~CS)
unnamed: U2.23 (PC0), U4.1 (~CS)
unnamed: U2.26 (PC3), U4.5 (MOSI)
unnamed: U2.27 (PC4), U4.6 (SCK)
unnamed: U2.28 (PC5), U4.2 (MISO)
unnamed: J3.1, U2.4 (PD2)
unnamed: J3.3, U2.5 (PD3)
unnamed: J3.5, U2.6 (PD4)
unnamed: J3.7, U2.11 (PD5)
unnamed: J3.9, U2.12 (PD6)
unnamed: R6.1, U2.13 (PD7)
unnamed: C5.1, U2.9 (XTAL1/PB6), Y1.1
unnamed: C9.1, U2.10 (XTAL2/PB7), Y1.2
unnamed: R12.1, U3.8 (Vout)
unnamed: C15.1, C18.2, R14.1, U5.3 (+)
unnamed: R17.2, R20.1, U5.5 (+)
unnamed: R18.1, R21.2, U5.6 (-)
RESET: J2.5, R2.1, S1.2, U2.1 (~RESET/PC6)
SCK: J2.7, U2.19 (PB5), U3.3 (SCK)
VIRTUAL GROUND: C15.2, C17.1, R14.2, R15.1, R16.2, R17.1, R18.2, R19.2, TP1.1

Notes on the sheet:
Op-amp B - Non-inverting amplifier for audio buffering
Power LED
AM modulator (signal mixer) and transmitter - Current-modulated cascode amplifier
Op-amp A - Wien bridge oscillator for the carrier wave
Reset circuit
USBasp programming header
Op-amp power section with virtual ground reference (2.5V)
Microcontroller circuit (USB to Serial conversion, AT command parsing, RTTY signal generation)
Audio output (optional, for headphones)

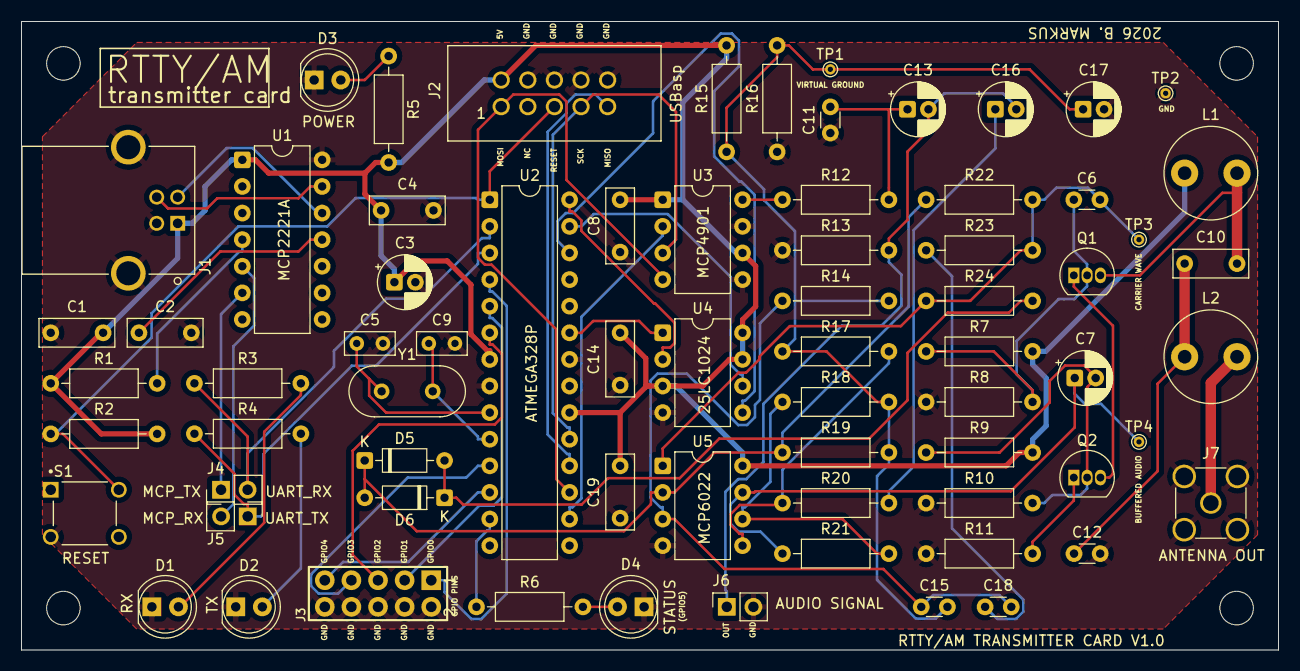
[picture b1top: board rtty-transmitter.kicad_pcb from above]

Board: 2 copper layers, 120.0 x 60.0 mm, 75 parts (0 on the bottom side), 51 nets.

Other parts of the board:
MH1, MH2, MH3, MH4: MountingHole_3.2mm_M3_DIN965

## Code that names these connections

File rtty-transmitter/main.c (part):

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 * =============================================================================
 *
 *  MCU         : ATmega328P (U2), 16 MHz crystal (Y1)
 *  USB-UART    : MCP2221A (U1) -  UART RX->PD0, TX->PD1
 *  DAC         : MCP4901 (U3) -  hardware SPI (PB5=SCK, PB3=MOSI, PB2=/CS)
 *  EEPROM      : 25LC1024 (U4)-  bit-bang SPI on PORTC (131072 bytes, 17-bit addr):
 *                    PC0 = /CS   (output)
 *                    PC3 = MOSI  (output)
 *                    PC4 = SCK   (output)
 *                    PC5 = MISO  (input)
 *  Status LED  : PD7 via R6   (output, active-high)
 *  GPIO header : PD2..PD6     (J3, user-accessible outputs)
 *  ISP header  : J2            (RESET, SCK, MISO, MOSI - for USBasp)
 *
 * =============================================================================
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 *                              params: high (Hz), low (Hz), baud (45.45 etc.)
 *  AT+get=<param>            - Read back a parameter value
 *                              params: high, low, baud
 *  AT+write=<pin>,<value>    - Drive a GPIO pin (pin 0-5 -> PD2-PD7, val 0/1)
 *  AT+play                   - Play 8-bit PCM audio stored in EEPROM
 *  AT+upload                 - Write raw hex bytes to EEPROM from UART stream
 *  AT+reset                  - Restore factory defaults (high/low/baud)
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

/* ============================================================================
 * STATUS LED  (PD7, active-high, cathode to GND via R6)
 * ============================================================================ */
#define LED_DDR   DDRD
#define LED_PORT  PORTD
#define LED_PIN   PD7

/** Drive the status LED on. This overrides any user-set value on that pin. */
#define LED_ON()  (LED_PORT |=  (1 << LED_PIN))
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#define SAMPLE_RATE    80000.0          /**< Timer1 ISR rate in Hz             */
#define CONFIG_HIGH    0x30U            /**< MCP4901 config: active, 1x gain   */

/** Hardware SPI chip-select for MCP4901 is PB2 (Arduino D10). */
#define DAC_CS_PORT  PORTB
#define DAC_CS_PIN   PB2

volatile uint32_t phaseAccumulator = 0;  /**< DDS phase accumulator (32-bit)  */
volatile uint32_t phaseIncrement   = 0;  /**< DDS step; 0 = carrier muted     */
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 * BIT-BANG SPI FOR 25LC1024 EEPROM  (PORTC)
 * ============================================================================
 *
 *  PC0 = /CS   (output) - active low chip select
 *  PC3 = MOSI  (output) - serial data in to EEPROM
 *  PC4 = SCK   (output) - clock (CPOL=0, CPHA=0)
 *  PC5 = MISO  (input)  - serial data out from EEPROM
 *
 * 25LC1024 SPI commands used here:
 *   READ  = 0x03  - sequential read from given 16-bit address
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 *   RDSR  = 0x05  - read status register (bit 0 = WIP write-in-progress)
 * ============================================================================ */

#define EE_CS_LOW()   (PORTC &= ~(1 << PC0))    /**< Assert /CS                */
#define EE_CS_HIGH()  (PORTC |=  (1 << PC0))    /**< Deassert /CS              */
#define EE_SCK_LOW()  (PORTC &= ~(1 << PC4))    /**< Clock low                 */
#define EE_SCK_HIGH() (PORTC |=  (1 << PC4))    /**< Clock high                */
#define EE_SI_HIGH()  (PORTC |=  (1 << PC3))    /**< MOSI high                 */
#define EE_SI_LOW()   (PORTC &= ~(1 << PC3))    /**< MOSI low                  */
#define EE_SO_READ()  ((PINC  &  (1 << PC5)) ? 1 : 0) /**< Read MISO          */

/** Total EEPROM capacity in bytes (25LC1024 = 1 Mbit = 131072 bytes). */
#define EEPROM_SIZE   131072UL
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 *  AT+send="..."    - Baudot-encode and transmit a message via RTTY
 *  AT+set=p,v       - Set parameter p (high|low|baud) to value v
 *  AT+get=p         - Query parameter p
 *  AT+write=p,v     - Drive GPIO pin p (0-5 -> PD2-PD7) to value v (0|1)
 *  AT+play          - Stream PCM audio from EEPROM through the DAC
 *  AT+upload        - Receive hex-encoded PCM data and write to EEPROM
 *  AT+reset         - Restore factory defaults
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            return;
        }

        /* Map logical pin 0-5 to PD2-PD7 (bit positions 2-7 in PORTD). */
        uint8_t bit = (uint8_t)(pin + 2);
        DDRD  |=  (1 << bit);                    /* Ensure pin is configured out */
        if (val) PORTD |=  (1 << bit);
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            "  AT+set=low,<Hz>            Set SPACE (low) frequency\r\n"
            "  AT+set=baud,<Bd>           Set symbol rate (e.g. 45.45)\r\n"
            "  AT+get=<high|low|baud>     Query a parameter value\r\n"
            "  AT+write=<pin>,<0|1>       Drive GPIO pin (0-5 = PD2-PD7)\r\n"
            "  AT+play                    Play PCM audio from EEPROM\r\n"
            "  AT+upload                  Write hex PCM data to EEPROM\r\n"
            "  AT+reset                   Restore factory defaults\r\n"
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    uart_puts_P(PSTR("    AT+send=\"msg\"      Transmit RTTY message\r\n"));
    uart_puts_P(PSTR("    AT+set=<p>,<v>     Set parameter (high/low/baud)\r\n"));
    uart_puts_P(PSTR("    AT+get=<p>         Query parameter\r\n"));
    uart_puts_P(PSTR("    AT+write=<p>,<v>   Set GPIO pin (0-5 -> PD2-PD7)\r\n"));
    uart_puts_P(PSTR("    AT+play            Play PCM audio from EEPROM\r\n"));
    uart_puts_P(PSTR("    AT+upload          Upload hex PCM data to EEPROM\r\n"));
    uart_puts_P(PSTR("    AT+reset           Restore factory defaults\r\n"));
    uart_puts_P(PSTR("    AT+help            Full command reference\r\n"));
    uart_puts_P(PSTR("\r\n"));
    uart_puts_P(PSTR("  Defaults: MARK=2125 Hz  SPACE=2295 Hz  BAUD=45.45\r\n"));
    uart_puts_P(PSTR("  Status LED: PD7 (lights during TX, upload, playback)\r\n"));
    uart_puts_P(PSTR("\r\n"));
    uart_puts_P(PSTR("  Ready.\r\n\r\n"));
}
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 *   1. UART  - set up first so debug/banner output works immediately.
 *   2. SPI   - hardware SPI for MCP4901 DAC.
 *   3. PORTC - bit-bang SPI pins for 25LC1024 EEPROM.
 *   4. PORTD - GPIO output pins (PD2-PD7) and status LED.
 *   5. Timer1 - 80 kHz DDS interrupt (started last to avoid ISR
 *               interfering with UART settling or banner output).
 */
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    uart_init();

    /* 2. Hardware SPI (MCP4901 DAC) ----------------------------------------- */
    /* PB2 = /CS (output), PB3 = MOSI (output), PB5 = SCK (output)            */
    DDRB |= (1 << PB2) | (1 << PB3) | (1 << PB5);
    DAC_CS_PORT |= (1 << DAC_CS_PIN);           /* Deassert /CS at startup     */

    /* Enable SPI as Master, SPI mode 0, MSB first.
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    SPSR = (1 << SPI2X);                        /* SPI2X=1: double to F_CPU/2 = 8 MHz */

    /* 3. PORTC bit-bang EEPROM ----------------------------------------------- */
    /* PC0=/CS, PC3=MOSI, PC4=SCK outputs; PC5=MISO input.                     */
    DDRC |=  (1 << PC0) | (1 << PC3) | (1 << PC4);
    DDRC &= ~(1 << PC5);
    EE_CS_HIGH();                                /* Deassert EEPROM /CS         */
    EE_SI_LOW();                                 /* MOSI idle low               */
    EE_SCK_LOW();                                /* SCK idle low                */

    /* 4. PORTD GPIO + LED ---------------------------------------------------- */
    /* PD2-PD7 as outputs (PD0=RX, PD1=TX are managed by UART peripheral).     */
    DDRD |= (1 << PD2) | (1 << PD3) | (1 << PD4)
          | (1 << PD5) | (1 << PD6) | (1 << LED_PIN);
    LED_OFF();                                   /* LED off at startup          */

    /* 5. Timer1: 80 kHz CTC for DDS ----------------------------------------- */
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
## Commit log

2024-05-11 Prototype Arduino code added
2026-01-08 Buzzer output pin changed to MCP4901 SPI DAC output with sinewave lookup table
2026-01-09 Initial schematic files added
2026-01-12 High-pass filter added after DAC output to remove DC offset
2026-01-12 Antenna amplifier and modulator-mixer added (current-modulated cascode amplifier), op-amp base circuits added
2026-01-13 Schematic: op-amp audio buffer refined
2026-01-13 Schematic: Jumpers added for RX/TX lines, audio output socket added
2026-01-13 Schematic: Test points added
2026-01-13 Schematic: Groups added
2026-01-13 Schematic: Labels reworked
2026-01-13 Schematic: USB Type B connector symbol updated
2026-01-13 Schematic: Test points and annotation updated
2026-01-13 PCB: Components updated
2026-01-15 PCB: SMA connector updated
2026-01-15 PCB: PCB layout updated
2026-01-15 PCB: Ground plane fill zones added
2026-01-15 PCB: Routing started
2026-01-15 PCB: Routing finished
2026-01-18 AT+play command added with 25LC1024 EEPROM support
2026-01-22 PCB updated: electrolytic capacitor footprints updated
2026-01-22 PCB updated: resistor footprints updated
2026-01-22 PCB: Gerber files added
2026-01-22 Schematic: wire redrawn, no functionality change
2026-03-02 Schematic migrated to KiCad 9
2026-03-02 White status LED current limiting resistor changed from 470R to 1k
2026-03-02 PCB footprints migrated to KiCad 9
2026-03-02 PCB migrated to KiCad 9
2026-03-02 Schematic and PCB LED colors updated
2026-03-07 Arduino code ported to bare-metal AVR C - MPLAB X IDE v6.25 project created
2026-03-07 AT+upload command implemented, MPLAB X IDE build configurations updated
2026-03-07 Python control center client app added to tools folder
2026-03-08 Control Center python application extended with file upload and comments added
2026-03-08 Documentation images and PDF schematic added
2026-03-08 Documentation image added: screenshot of carrier wave frequency counter
2026-03-09 Added AM vs. SSB graph to docs/images
2026-03-09 LTspice simulation files added for AM modulator
2026-03-09 LTspice simulation screenshot added to docs/images
2026-03-10 Block diagram added to docs/images
2026-03-23 Added 8-bit unsigned PCM 8KHz audio samples to assets/pcm-samples, ready to upload to the board
